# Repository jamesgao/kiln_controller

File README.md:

Raspberry Pi controlled Kiln
============================

This project implements a wifi-accessible temperature controller for a ceramic firing kiln.

Please see the BOM for all the parts we purchased for this project. Additional circuit diagrams and 3D models will be forthcoming.

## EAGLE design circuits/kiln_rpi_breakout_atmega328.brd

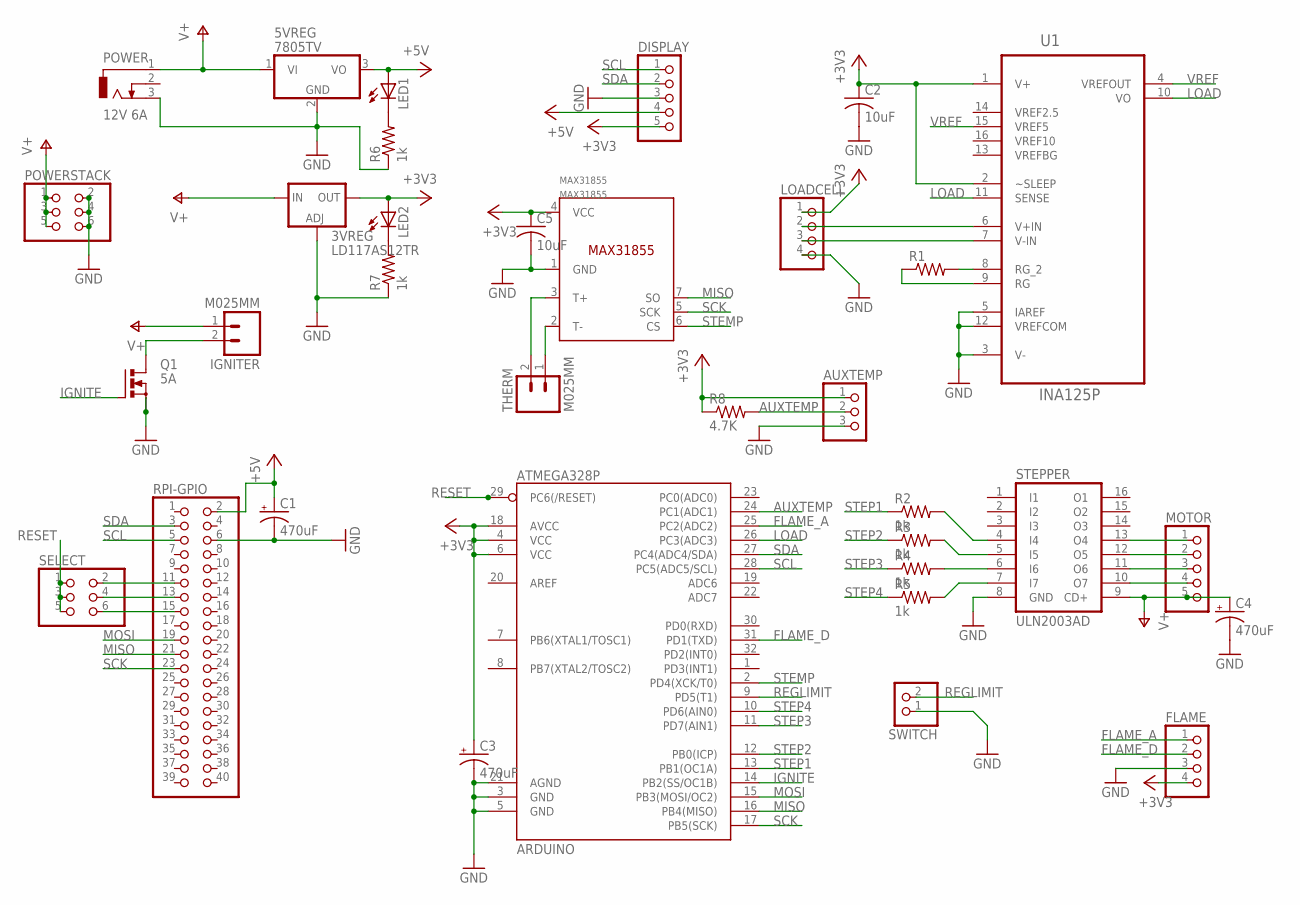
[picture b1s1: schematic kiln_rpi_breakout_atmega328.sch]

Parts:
3VREG: LD117AS12TR; SOT223
5VREG: 7805TV; TO220V
ARDUINO: ATMEGA328P; TQFP32-08
AUXTEMP: PINHD-1X3; 1X03
C1, C3, C4: 470uF; E3,5-8
C2, C5: 10uF; C025-030X050
DISPLAY: PINHD-1X5; 1X05
FLAME: PINHD-1X4/90; 1X04/90
IGNITER: M025MM; SCREWTERMINAL-5MM-2
LED1, LED2: LED3MM
LOADCELL: PINHD-1X4/90; 1X04/90
MAX31855: MAX31855; SOIC8
MOTOR: PINHD-1X5/90; 1X05/90
POWER: 12V 6A; DCJ0303
POWERSTACK: PINHD-2X3; 2X03
Q1: 5A; TO220BV
R1: R-US_0204/7; 0204/7
R2, R3, R4, R5, R6, R7: 1k; 0207/7
R8: 4.7K; 0207/2V
RPI-GPIO: PINHD-2X20; 2X20
SELECT: PINHD-2X3; 2X03
STEPPER: ULN2003AD; SO16
SWITCH: PINHD-1X2/90; 1X02/90
THERM: M025MM; SCREWTERMINAL-5MM-2
U1: INA125P; DIP254P762X508-16

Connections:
+3V3: 3VREG.4 (OUT), ARDUINO.4 (VCC), ARDUINO.6 (VCC), ARDUINO.18 (AVCC), AUXTEMP.1, C2.1, C3.+, C5.1, DISPLAY.5, FLAME.4, LED2.A, LOADCELL.1, MAX31855.4 (VCC), R8.1, U1.1 (V+), U1.2 (~SLEEP)
+5V: 5VREG.3 (VO), C1.+, DISPLAY.4, LED1.A, RPI-GPIO.2
AUXTEMP: ARDUINO.24 (PC1(ADC1)), AUXTEMP.2, R8.2
FLAME_A: ARDUINO.25 (PC2(ADC2)), FLAME.1
FLAME_D: ARDUINO.31 (PD1(TXD)), FLAME.2
GND: 3VREG.1 (ADJ), 5VREG.2 (GND), ARDUINO.3 (GND), ARDUINO.5 (GND), ARDUINO.21 (AGND), AUXTEMP.3, C1.-, C2.2, C3.-, C4.-, C5.2, DISPLAY.3, FLAME.3, LOADCELL.4, MAX31855.1 (GND), POWER.3, POWERSTACK.2, POWERSTACK.4, POWERSTACK.6, Q1.S, R6.1, R7.1, RPI-GPIO.6, STEPPER.8 (GND), SWITCH.1, U1.3 (V-), U1.5 (IAREF), U1.12 (VREFCOM)
IGNITE: ARDUINO.14 (PB2(SS/OC1B)), Q1.G
LOAD: ARDUINO.26 (PC3(ADC3)), U1.10 (VO), U1.11 (SENSE)
MISO: ARDUINO.16 (PB4(MISO)), MAX31855.7 (SO), RPI-GPIO.21
MOSI: ARDUINO.15 (PB3(MOSI/OC2)), RPI-GPIO.19
unnamed: MOTOR.1, STEPPER.13 (O4)
unnamed: MOTOR.2, STEPPER.12 (O5)
unnamed: MOTOR.3, STEPPER.11 (O6)
unnamed: MOTOR.4, STEPPER.10 (O7)
unnamed: LED1.K (C), R6.2
unnamed: LOADCELL.2, U1.6 (V+IN)
unnamed: LOADCELL.3, U1.7 (V-IN)
unnamed: MAX31855.3 (T+), THERM.2
unnamed: IGNITER.2, Q1.D
unnamed: R1.2, U1.8 (RG_2)
unnamed: R5.2, STEPPER.7 (I7)
unnamed: R4.2, STEPPER.6 (I6)
unnamed: R3.2, STEPPER.5 (I5)
unnamed: R2.2, STEPPER.4 (I4)
unnamed: R1.1, U1.9 (RG)
unnamed: MAX31855.2 (T-), THERM.1
unnamed: LED2.K (C), R7.2
REGLIMIT: ARDUINO.9 (PD5(T1)), SWITCH.2
RESET: ARDUINO.29 (PC6(/RESET)), SELECT.1, SELECT.3, SELECT.5
RESET1: RPI-GPIO.11, SELECT.2
RESET2: RPI-GPIO.13, SELECT.4
RESET3: RPI-GPIO.15, SELECT.6
SCK: ARDUINO.17 (PB5(SCK)), MAX31855.5 (SCK), RPI-GPIO.23
SCL: ARDUINO.28 (PC5(ADC5/SCL)), DISPLAY.1, RPI-GPIO.5
SDA: ARDUINO.27 (PC4(ADC4/SDA)), DISPLAY.2, RPI-GPIO.3
STEMP: ARDUINO.2 (PD4(XCK/T0)), MAX31855.6 (CS)
STEP1: ARDUINO.13 (PB1(OC1A)), R2.1
STEP2: ARDUINO.12 (PB0(ICP)), R3.1
STEP3: ARDUINO.11 (PD7(AIN1)), R4.1
STEP4: ARDUINO.10 (PD6(AIN0)), R5.1
V+: 3VREG.3 (IN), 5VREG.1 (VI), C4.+, IGNITER.1, MOTOR.5, POWER.1, POWERSTACK.1, POWERSTACK.3, POWERSTACK.5, STEPPER.9 (CD+)
VREF: U1.4 (VREFOUT), U1.15 (VREF5)
VREF2.5: U1.14 (VREF2.5)
VREF10: U1.16 (VREF10)
VREFBG: U1.13 (VREFBG)

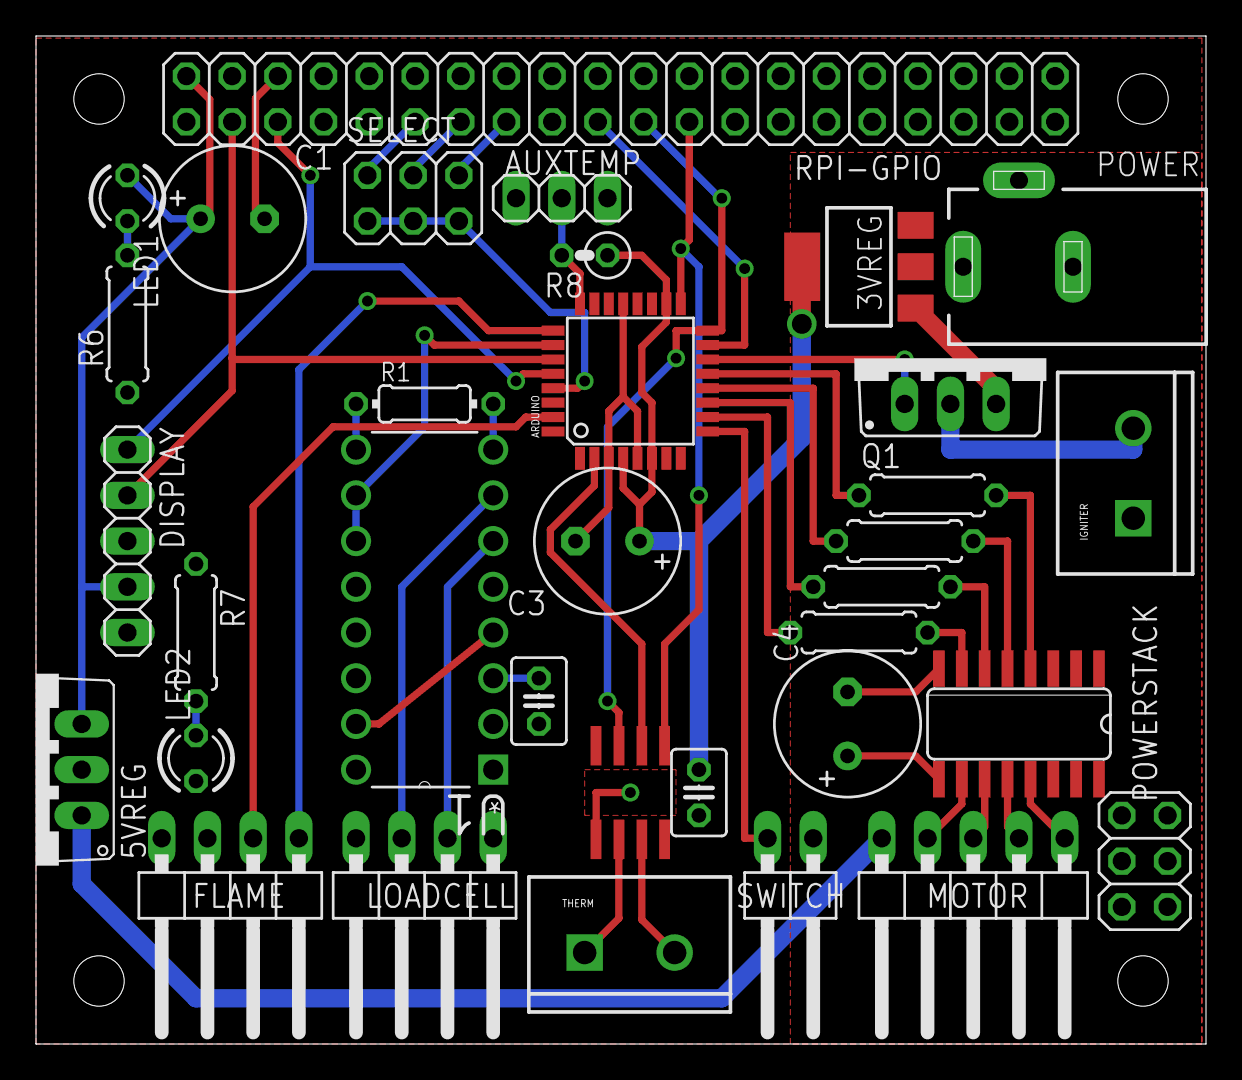
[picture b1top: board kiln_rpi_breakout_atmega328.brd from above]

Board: 2 copper layers, 65.0 x 56.0 mm, 34 parts (0 on the bottom side), 42 nets.

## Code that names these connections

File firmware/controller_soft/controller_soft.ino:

#define PIN_IGNITE    10
#define PIN_STEP1     9
#define PIN_STEP2     8
#define PIN_STEP3     7
#define PIN_STEP4     6
#define PIN_AUXTEMP   A1
#define PIN_TEMP_CS   4
#define PIN_LOADCELL  A3
#define PIN_FLAME_A   A2
#define PIN_FLAME_D   1
#define PIN_REGLIMIT  5

#define STEP_SPEED 275//in steps per second
#define TEMP_UPDATE 250 //milliseconds
#define MOTOR_TIMEOUT 5000 //milliseconds

#define NO_PORTB_PINCHANGES
#define NO_PORTC_PINCHANGES
#define DISABLE_PCINT_MULTI_SERVICE

#include <Stepper.h>
#include <Wire.h>
#include <SPI.h>
#include <Adafruit_MAX31855.h>
#include <ooPinChangeInt.h>
#include "pushbutton.h"

struct Status {
  unsigned char ignite;
  unsigned char flame;
  unsigned int motor;
  float main_temp;
  float ambient;
  float weight;
  float aux_temp[2];
} status;
uint8_t* status_data = (uint8_t*) &status;

const float step_interval = 1. / STEP_SPEED * 1000.; //milliseconds

//intermediate variables
Adafruit_MAX31855 thermo(PIN_TEMP_CS);
Stepper stepper(2048, PIN_STEP4, PIN_STEP2, PIN_STEP3, PIN_STEP1);
pushbutton reglimit = pushbutton(PIN_REGLIMIT, 5);

char i2c_command;
float next_step;
unsigned long next_temp;
unsigned char motor_active = false;
unsigned long stepper_target = 0;
int n_clicks = 0; //Number of full rotations
boolean limit_state = false;
unsigned long limit_last;

void setup() {
  status.flame = false;
  status.weight = 0.;
  status.aux_temp[0] = 0.;
  status.aux_temp[1] = 0.;
  
  //Setup I2C
  Wire.begin(0x08);
  Wire.onRequest(i2c_update);
  Wire.onReceive(i2c_action);
  
  //Set up regulator stepper
  status.motor = 0;
  
  //setup ignition mosfet
  pinMode(PIN_IGNITE, OUTPUT);
  digitalWrite(PIN_IGNITE, LOW);
  status.ignite = false;
  
  //set initial temperature
  delay(500);
  update_temp();
  next_temp = millis() + TEMP_UPDATE;
}

int dir;
unsigned long now;
void loop() {
  now = millis();
  reglimit.update();
  status.aux_temp[0] = reglimit.n_clicks;
  
  if (stepper_target != status.motor && now > next_step) {
    dir = status.motor < stepper_target ? 1 : -1;
    stepper.step(dir);
    
    //Limit switch tripped
    if (stepper_target == 0) {
      if (reglimit.n_clicks == 0)
        status.motor = 0;
    } else {
      status.motor += dir;
    }
    
    next_step += step_interval;
  }
  
  //put motor to sleep after timeout
  if (motor_active && (now - next_step) > MOTOR_TIMEOUT) {
    digitalWrite(PIN_STEP1, LOW);
    digitalWrite(PIN_STEP2, LOW);
    digitalWrite(PIN_STEP3, LOW);
    digitalWrite(PIN_STEP4, LOW);
    motor_active = false;
  }
  
  //update temperature
  if (now > next_temp) {
    update_temp();
    next_temp += TEMP_UPDATE;
  }
  
  //check flame status
}

void set_regulator(unsigned long pos) {
  motor_active = true;
  reglimit.setDir(status.motor < pos ? 1 : -1);
  if (stepper_target == status.motor)
    next_step = millis(); //Start stepping immediately
  stepper_target = pos;
}

void update_temp() {
  thermo.readAll(status.main_temp, status.ambient);
}

void i2c_update() {
  //update temperatures
  
  if (i2c_command == 'M') {
    Wire.write((byte*) &(status.motor), 4);
  } else if (i2c_command == 'I') {
    Wire.write((byte*) &(status.ignite), 1);
  } else if (i2c_command == 'T') {
    Wire.write((byte*) &(status.main_temp), 4);
  } else if (i2c_command == 'F') {
    Wire.write((byte*) &(status.flame), 1);
  } else {
    Wire.write(status_data, sizeof(struct Status));
  }
  
  i2c_command = 0;
}

byte buffer[32];
void i2c_action(int nbytes) {
  i2c_command = Wire.read();
  
  int i = 0;
  while (Wire.available()) {
    buffer[i++] = Wire.read();
  }
  
  if (nbytes == 1) {
    return; //Command already stored, no arguments
  }
  
  switch (i2c_command) {
    case 'M':
      set_regulator(*((unsigned int*) buffer));
      break;
    case 'I':
      analogWrite(PIN_IGNITE, buffer[0]);
      status.ignite = buffer[0];
      break;
  }
  
  i2c_command = 0;
}

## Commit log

2014-10-15 Implement the stepper-controlled regulator function
2014-10-15 Set up stepper.py for the limits
2014-10-15 Move everything for github commit
2014-10-15 Add additional LED code
2014-10-15 Add current thermocouple reading code
2014-10-16 created KilnController class which sets the kiln temperature according to a schedule using PID temperature control
2014-10-16 Adding temp monitor code
2014-10-16 Fix up typos
2014-10-16 Fixing threading, dot rendering
2014-10-16 Forgot to *args for alphascroller
2014-10-16 Working thermo.py with LED scroller
2014-10-16 Only display temperature above 50 C
2014-10-17 update nonblocking stepper, damn is bootstrap sexy
2014-10-17 working on d3 graph for temperature
2014-10-17 Add the scad and stl files for kiln parts
2014-10-17 Add a readme
2014-10-18 Add some test code
2014-10-18 Forgot to fix the thermocouple display
2014-10-18 Fix bugs in stepper
2014-10-18 Still fixing small bugs in stepper, now tested
2014-10-18 Add a bunch of simulation code to test PID
2014-10-18 add temperature logging with a file
2014-10-18 Update from actual testing
2014-10-19 update the settings for successful firing
2014-10-19 Working zoom behavior for the tempgraph
2014-10-20 testing temperature streaming
2014-10-20 Forgot some imports
2014-10-20 Forgot to actually activate the websocket
2014-10-20 working server for streaming temperature data
2014-10-20 Attempting to fix #1
2014-10-20 Actually fix #1
2014-10-21 starting to work on state machine for backend
2014-10-22 Backend state machine likely finished, need to test
2014-10-22 Convert BOM to markdown
2014-10-22 Add power supply, total to BOM.md
2014-10-22 Backend state machine finished, untested
2014-10-23 State machine done: #3. Manual override works
2014-10-23 move files around, add local js/css, start profiles
2014-10-23 Forgot to commit paths.py for the reorganiation
2014-10-25 Profile display now works
2014-10-26 Add code / model for a limit switch
2014-10-29 Finished circuit boards sent out
    Finally finished the circuit board design. I ended up going with a
    pretty different approach than I was originally planning, since this
    design is low impact and allows board stacking. An ATMEGA328 chip
    running as an I2C slave will be the primary communication between the
    raspberry pi and the hardware, instead of the raspberry pi directly
    controlling the hardware. Code changes to accommodate will be
2014-10-29 Add auxtemp header, stacking power connector
    Managed to update the pcb order in time. Auxtemp header takes a DS18B20
    chip as an auxiliary temperature monitor, good for checking for propane
    tank freezing or even as primary temperature control. Additional
    powerstack header allows stacked breakouts to pass power between boards
2014-11-01 Node dragging works, no saving yet
2014-11-02 Profile editing now working
    Still need to allow profile saving and understanding state changes
    throughout
2014-11-02 Schedule saving complete, add pcb images
    Most of the UI elements behave as expected, but setting the Running
    state is not yet complete. Still need to work out how to deal with the
    profile names on the server side. Added a couple of images for the PCB.
    Rendered version of the pcb is care of dirtypcb.com, where I ordered the
    first batch of PCBs. The other image is rendered via EagleCAD.
2014-11-27 Adding firmware interface for circuitboard
2014-11-27 Add preliminary arduino firmware code
2014-11-29 Software now supports breakout board
2014-11-29 Fixes to make new code work with actual device
2014-11-30 Working profile running, events still need work
2014-11-30 fix nan problem
2014-11-30 JSON has immense hatred of NaN values
2014-11-30 Add some smoothing
2014-11-30 Minor: typo
2014-11-30 update defaults to be in the right direction
2014-11-30 Fix defaults again, first ones were errant
2014-11-30 Add some spike detection in temperature
2014-12-17 Bug fixes from last firing
2015-02-22 add ds18b20 reading to firmware
2015-02-22 added graph.resample method to prevent browser crash from trying to plot too many points
2015-02-22 minor
2015-02-22 interpolate minstep for temperature
2015-02-22 lower the min motor
2015-02-22 Lower limits for stepper
2015-02-22 implement rudimentary duty-cycle support
2015-02-22 Only re-ignite if temperature at least 20 degrees below setpoint
2015-02-22 logic error in duty cycling
2015-02-22 Better timing for PID loop
2015-02-22 typos
2015-02-23 don't resample if total number of points is below threshold
2017-11-25 Corrected the table in README.md

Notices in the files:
parts and their libraries:
SparkFun-Connectors: Licensing: Creative Commons ShareAlike 4.0 International - https://creativecommons.org/licenses/by-sa/4.0
